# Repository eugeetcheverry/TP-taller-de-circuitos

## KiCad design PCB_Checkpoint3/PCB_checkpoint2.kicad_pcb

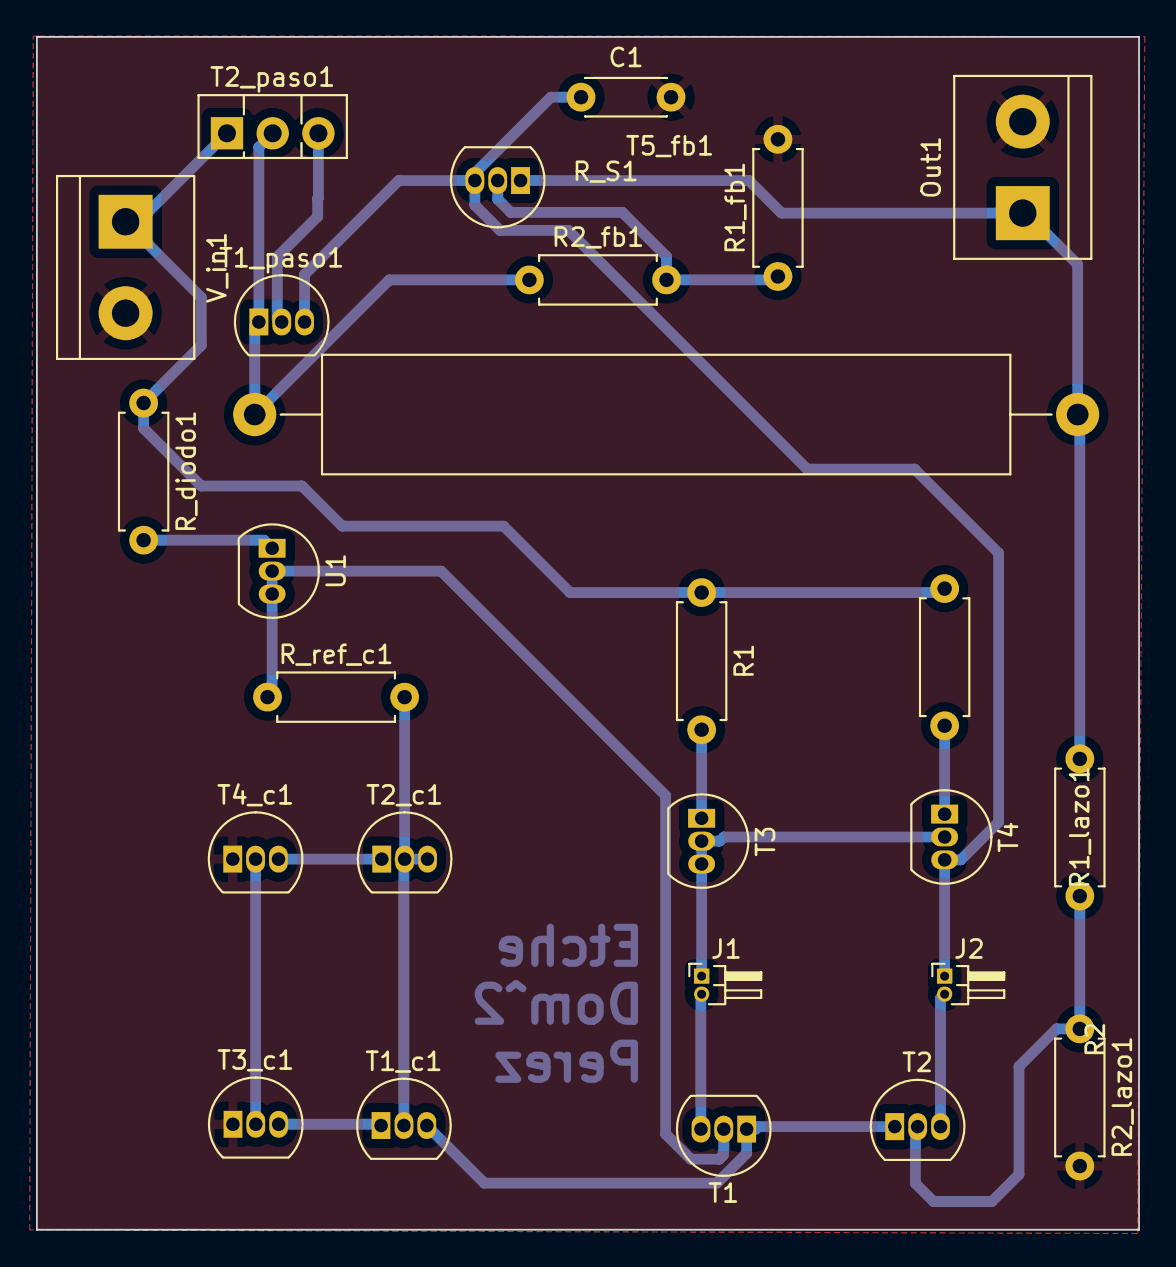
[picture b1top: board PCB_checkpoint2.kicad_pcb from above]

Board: 2 copper layers, 61.2 x 66.3 mm, 26 parts (0 on the bottom side), 19 nets.

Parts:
C1: 68n; C_Disc_D4.3mm_W1.9mm_P5.00mm
J1, J2: Conn_01x02_Male; PinHeader_1x02_P1.00mm_Horizontal
Out1: Conn_01x02_Female; TerminalBlock_bornier-2_P5.08mm
R1, R2: 2.2K; R_Axial_DIN0207_L6.3mm_D2.5mm_P7.62mm_Horizontal
R1_fb1: 2.32K; R_Axial_DIN0207_L6.3mm_D2.5mm_P7.62mm_Horizontal
R1_lazo1, R2_lazo1: 100K; R_Axial_DIN0207_L6.3mm_D2.5mm_P7.62mm_Horizontal
R2_fb1: 1K; R_Axial_DIN0207_L6.3mm_D2.5mm_P7.62mm_Horizontal
R_S1: 2; R_Axial_Power_L38.0mm_W6.4mm_P45.72mm
R_diodo1: 2.3K; R_Axial_DIN0207_L6.3mm_D2.5mm_P7.62mm_Horizontal
R_ref_c1: 3K; R_Axial_DIN0207_L6.3mm_D2.5mm_P7.62mm_Horizontal
T1, T1_c1, T1_paso1, T2, T2_c1, T3_c1, T4_c1, T5_fb1: 2N3904; TO-92_Inline
T2_paso1: TIP32C; TO-126-3_Vertical
T3, T4: 2N3906; TO-92_Inline
U1: TL431D; TO-92_Inline
V_in1: 9.5; TerminalBlock_bornier-2_P5.08mm

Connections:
GND: C1.2, Out1.2, R1_fb1.2, R2_lazo1.2, T3_c1.1 (E), T4_c1.1 (E), V_in1.2 (-)
unnamed: J1.1, T3.2 (B), T3.3 (C), T4.2 (B)
unnamed: J1.2, T1.3 (C)
unnamed: C1.1, J2.1, T1_paso1.3 (B), T4.3 (C), T5_fb1.3 (C)
unnamed: J2.2, T2.3 (C)
unnamed: Out1.1, R1_lazo1.1, R_S1.2, T5_fb1.1 (E)
unnamed: R_ref_c1.1, T1.2 (B), U1.2 (A), U1.3 (A)
unnamed: T1.1 (E), T1_c1.3 (C), T2.1 (E)
unnamed: R_ref_c1.2, T1_c1.2 (B), T2_c1.2 (B), T2_c1.3 (C)
unnamed: T1_c1.1 (E), T3_c1.3 (C)
unnamed: T1_paso1.2 (C), T2_paso1.3 (B)
unnamed: R2_fb1.1, R_S1.1, T1_paso1.1 (E), T2_paso1.2 (C)
unnamed: R1_lazo1.2, R2_lazo1.1, T2.2 (B)
unnamed: T2_c1.1 (E), T3_c1.2 (B), T4_c1.2 (B), T4_c1.3 (C)
unnamed: R1.1, R2.1, R_diodo1.1, T2_paso1.1 (E), V_in1.1 (+)
unnamed: R1.2, T3.1 (E)
unnamed: R2.2, T4.1 (E)
unnamed: R1_fb1.1, R2_fb1.2, T5_fb1.2 (B)
unnamed: R_diodo1.2, U1.1 (K)

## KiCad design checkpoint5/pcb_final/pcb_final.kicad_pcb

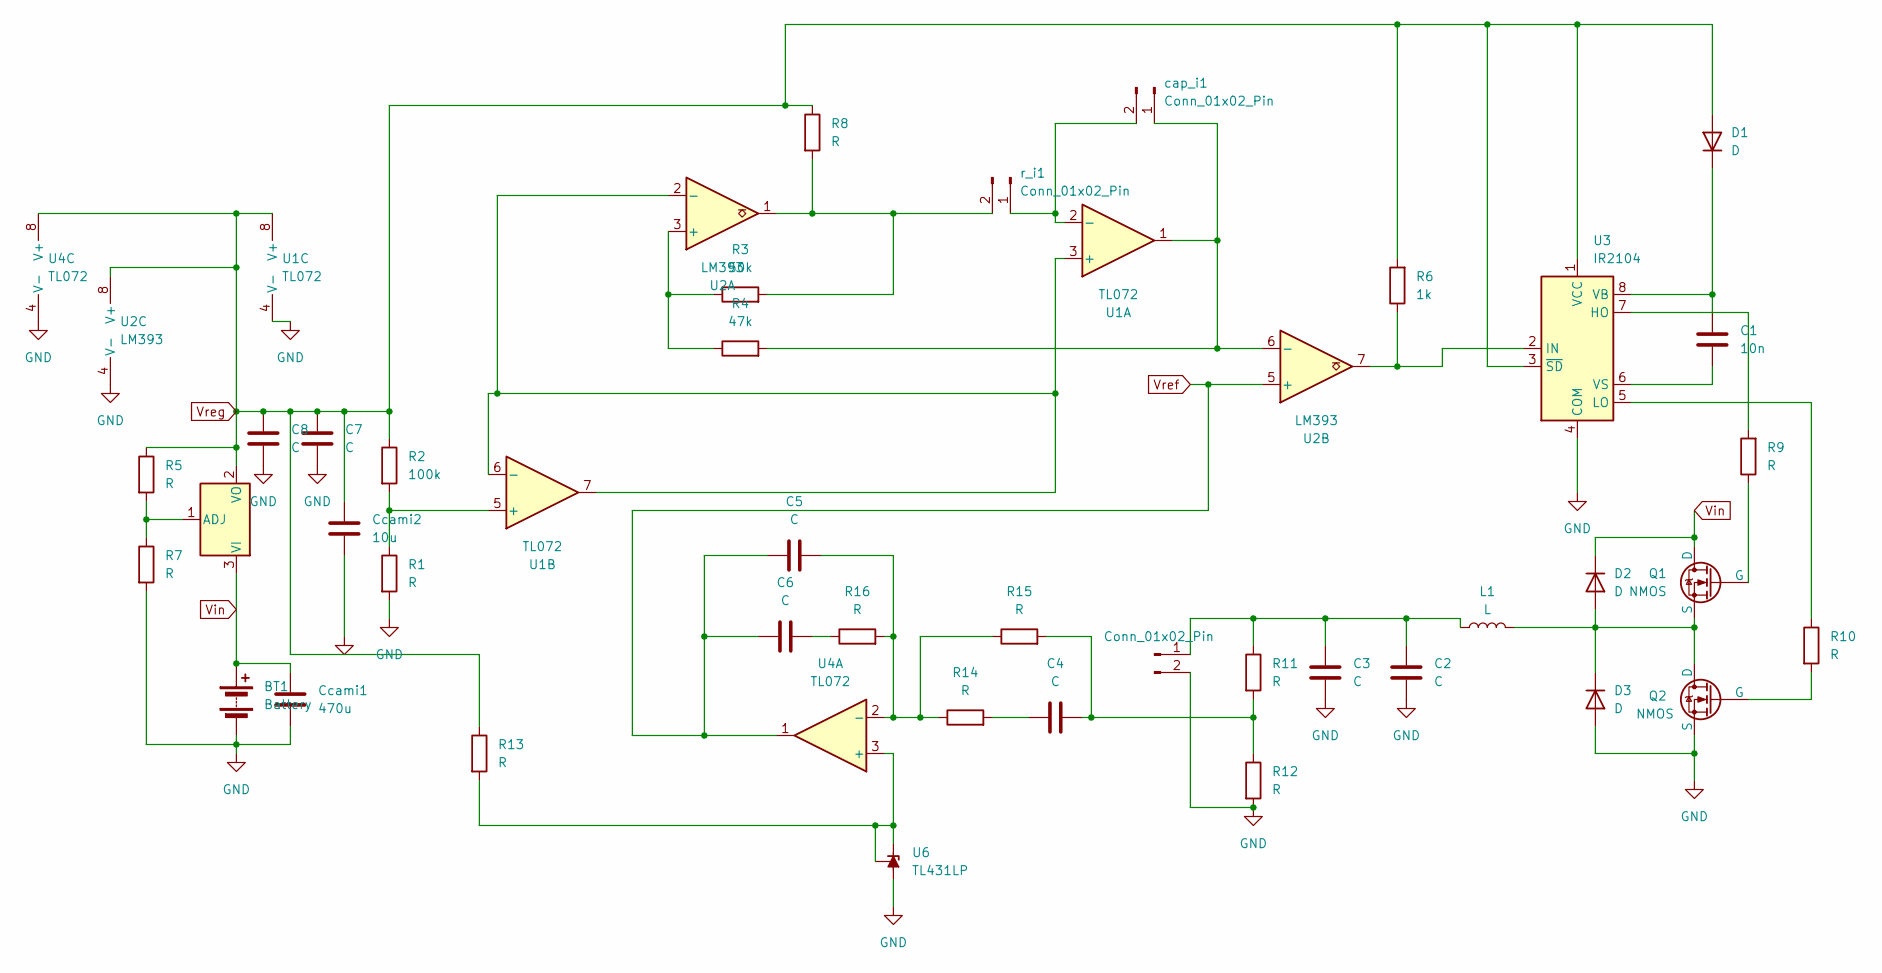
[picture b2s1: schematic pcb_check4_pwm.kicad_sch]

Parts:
BT1: Battery; TerminalBlock_bornier-2_P5.08mm
C1: 10n; C_Axial_L5.1mm_D3.1mm_P7.50mm_Horizontal
C2, C3, C4, C5, C6: C; C_Axial_L5.1mm_D3.1mm_P7.50mm_Horizontal
C7, C8: C; C_Axial_L3.8mm_D2.6mm_P10.00mm_Horizontal
Ccami1: 470u; CP_Radial_D5.0mm_P2.50mm
Ccami2: 10u; C_Axial_L5.1mm_D3.1mm_P10.00mm_Horizontal
D1, D2, D3: D; D_5W_P5.08mm_Vertical_AnodeUp
J1: Conn_01x02_Pin; TerminalBlock_bornier-2_P5.08mm
L1: L; Transformer_CHK_EI38-3VA_Neutral
Q1, Q2: NMOS; SIPAK_Vertical
R1, R5, R7, R8, R10, R11, R12, R13, R14, R15, R16: R; R_Axial_DIN0207_L6.3mm_D2.5mm_P7.62mm_Horizontal
R2: 100k; R_Axial_DIN0207_L6.3mm_D2.5mm_P7.62mm_Horizontal
R3: 50k; R_Axial_DIN0207_L6.3mm_D2.5mm_P7.62mm_Horizontal
R4: 47k; R_Axial_DIN0207_L6.3mm_D2.5mm_P7.62mm_Horizontal
R6: 1k; R_Axial_DIN0207_L6.3mm_D2.5mm_P7.62mm_Horizontal
R9: R; R_Axial_DIN0207_L6.3mm_D2.5mm_P10.16mm_Horizontal
U1, U4: TL072; CERDIP-8_W7.62mm_SideBrazed_LongPads
U2: LM393; CERDIP-8_W7.62mm_SideBrazed_LongPads
U3: IR2104; CERDIP-8_W7.62mm_SideBrazed_LongPads
U5: LM317L_SOT-89; TO-92_Inline
U6: TL431LP; TO-92_Inline
cap_i1: Conn_01x02_Pin; PinHeader_1x02_P1.00mm_Vertical
r_i1: Conn_01x02_Pin; PinHeader_1x02_P1.00mm_Vertical

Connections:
GND: BT1.2 (-), C2.2, C3.2, C7.2, C8.2, Ccami1.2, Ccami2.2, D3.2 (A), J1.2, Q2.3 (S), R1.2, R7.2, R12.2, U1.4 (V-), U2.4 (V-), U3.4 (COM), U4.4 (V-), U6.2 (A)
unnamed: C4.1, R14.2
unnamed: C4.2, R11.2, R12.1, R15.2
unnamed: C6.2, R16.1
unnamed: D2.2 (A), D3.1 (K), L1.2, Q1.3 (S), Q2.1 (D)
unnamed: C2.1, C3.1, J1.1, L1.1, R11.1
unnamed: Q1.2 (G), R9.1
unnamed: Q2.2 (G), R10.2
unnamed: U1.3 (+), U1.6 (-), U1.7, U2.2 (-)
unnamed: U1.2 (-), cap_i1.2, r_i1.1
unnamed: R1.1, R2.2, U1.5 (+)
unnamed: R3.1, R4.1, U2.3 (+)
unnamed: R4.2, U1.1, U2.6 (-), cap_i1.1
unnamed: R6.1, U2.7, U3.2 (IN)
unnamed: R10.1, U3.5 (LO)
unnamed: C1.2, U3.6 (VS)
unnamed: R13.2, U4.3 (+), U6.1 (REF), U6.3 (K)
unnamed: C5.2, R14.1, R15.1, R16.2, U4.2 (-)
unnamed: R5.2, R7.1, U5.1 (ADJ)
unnamed: R3.2, R8.2, U2.1, r_i1.2
Vin: BT1.1 (+), Ccami1.1, D2.1 (K), Q1.1 (D), U5.3 (VI)
Vref: C5.1, C6.1, U2.5 (+), U4.1
Vreg: C7.1, C8.1, Ccami2.1, D1.2 (A), R2.1, R5.1, R6.2, R8.1, R13.1, U1.8 (V+), U2.8 (V+), U3.1 (VCC), U3.3 (~SD), U4.8 (V+), U5.2 (VO)

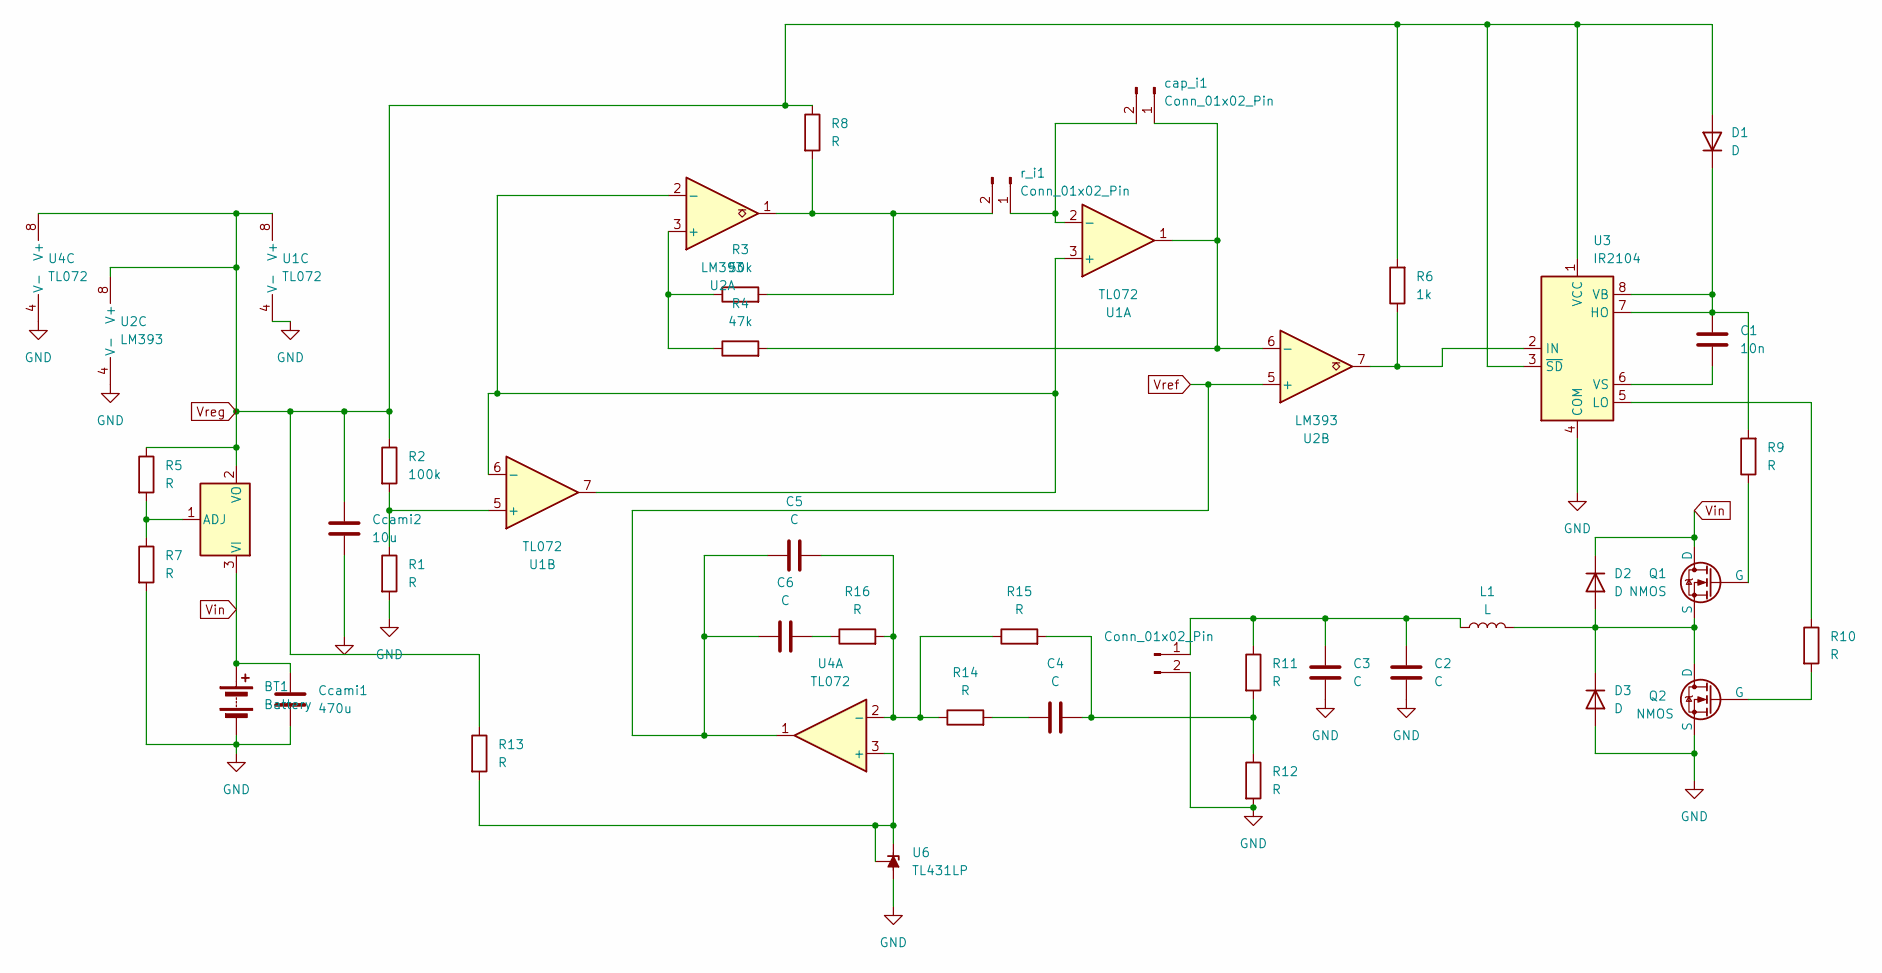
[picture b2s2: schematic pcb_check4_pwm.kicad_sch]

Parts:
BT1: Battery; TerminalBlock_bornier-2_P5.08mm
C1: 10n; C_Axial_L5.1mm_D3.1mm_P7.50mm_Horizontal
C2, C3, C4, C5, C6: C; C_Axial_L5.1mm_D3.1mm_P7.50mm_Horizontal
Ccami1: 470u; CP_Radial_D5.0mm_P2.50mm
Ccami2: 10u; C_Axial_L5.1mm_D3.1mm_P10.00mm_Horizontal
D1, D2, D3: D; D_5W_P5.08mm_Vertical_AnodeUp
J1: Conn_01x02_Pin; TerminalBlock_bornier-2_P5.08mm
L1: L; Transformer_CHK_EI38-3VA_Neutral
Q1, Q2: NMOS; SIPAK_Vertical
R1, R5, R7, R8, R10, R11, R12, R13, R14, R15, R16: R; R_Axial_DIN0207_L6.3mm_D2.5mm_P7.62mm_Horizontal
R2: 100k; R_Axial_DIN0207_L6.3mm_D2.5mm_P7.62mm_Horizontal
R3: 50k; R_Axial_DIN0207_L6.3mm_D2.5mm_P7.62mm_Horizontal
R4: 47k; R_Axial_DIN0207_L6.3mm_D2.5mm_P7.62mm_Horizontal
R6: 1k; R_Axial_DIN0207_L6.3mm_D2.5mm_P7.62mm_Horizontal
R9: R; R_Axial_DIN0207_L6.3mm_D2.5mm_P10.16mm_Horizontal
U1, U4: TL072; CERDIP-8_W7.62mm_SideBrazed_LongPads
U2: LM393; CERDIP-8_W7.62mm_SideBrazed_LongPads
U3: IR2104; CERDIP-8_W7.62mm_SideBrazed_LongPads
U5: LM317L_SOT-89; TO-92_Inline
U6: TL431LP; TO-92_Inline
cap_i1: Conn_01x02_Pin; PinHeader_1x02_P1.00mm_Vertical
r_i1: Conn_01x02_Pin; PinHeader_1x02_P1.00mm_Vertical

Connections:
GND: BT1.2 (-), C2.2, C3.2, Ccami1.2, Ccami2.2, D3.2 (A), J1.2, Q2.3 (S), R1.2, R7.2, R12.2, U1.4 (V-), U2.4 (V-), U3.4 (COM), U4.4 (V-), U6.2 (A); also elsewhere on the board
unnamed: C4.1, R14.2
unnamed: C4.2, R11.2, R12.1, R15.2
unnamed: C6.2, R16.1
unnamed: D2.2 (A), D3.1 (K), L1.2, Q1.3 (S), Q2.1 (D)
unnamed: C2.1, C3.1, J1.1, L1.1, R11.1
unnamed: Q1.2 (G), R9.1
unnamed: Q2.2 (G), R10.2
unnamed: U1.3 (+), U1.6 (-), U1.7, U2.2 (-)
unnamed: U1.2 (-), cap_i1.2, r_i1.1
unnamed: R1.1, R2.2, U1.5 (+)
unnamed: R3.1, R4.1, U2.3 (+)
unnamed: R4.2, U1.1, U2.6 (-), cap_i1.1
unnamed: R6.1, U2.7, U3.2 (IN)
unnamed: R10.1, U3.5 (LO)
unnamed: C1.2, U3.6 (VS)
unnamed: R13.2, U4.3 (+), U6.1 (REF), U6.3 (K)
unnamed: C5.2, R14.1, R15.1, R16.2, U4.2 (-)
unnamed: R5.2, R7.1, U5.1 (ADJ)
unnamed: R3.2, R8.2, U2.1, r_i1.2
Vin: BT1.1 (+), Ccami1.1, D2.1 (K), Q1.1 (D), U5.3 (VI)
Vref: C5.1, C6.1, U2.5 (+), U4.1
Vreg: Ccami2.1, D1.2 (A), R2.1, R5.1, R6.2, R8.1, R13.1, U1.8 (V+), U2.8 (V+), U3.1 (VCC), U3.3 (~SD), U4.8 (V+), U5.2 (VO); also elsewhere on the board

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
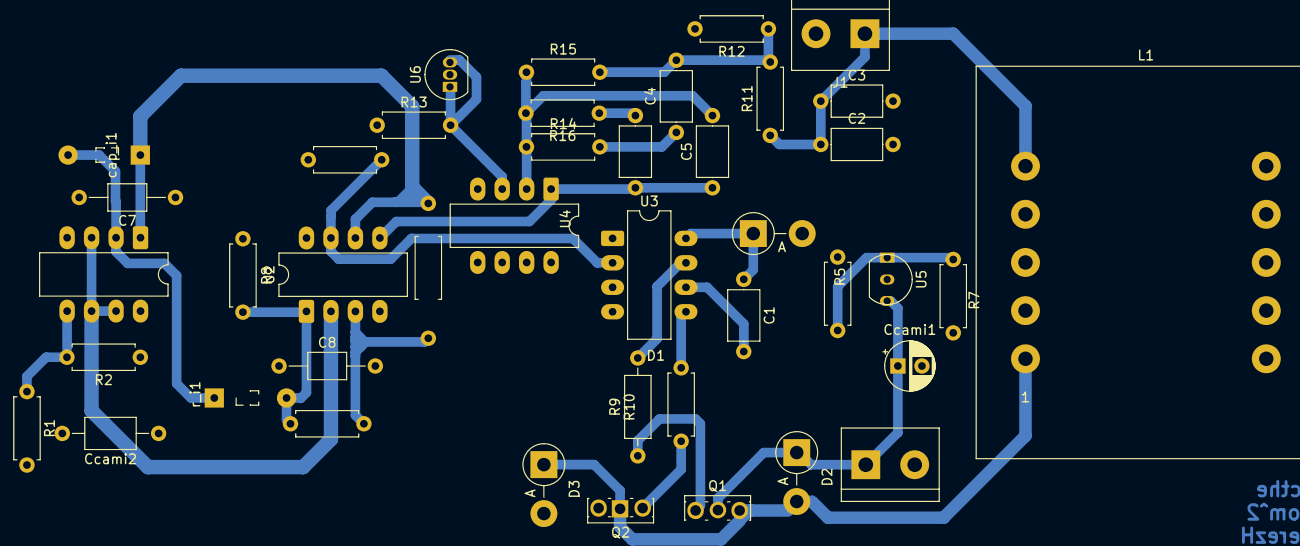
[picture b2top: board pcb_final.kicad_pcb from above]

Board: 2 copper layers, 42 parts (0 on the bottom side), 25 nets.
